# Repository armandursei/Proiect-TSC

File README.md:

# OpenBook e-Reader

Hardware design of **OpenBook**, a low-power, open-source e-book reader built around the
**ESP32-C6** (Wi-Fi 6 + Bluetooth LE, RISC-V). The repository contains the complete design
package: schematic and 2-layer PCB, manufacturing outputs (Gerbers, BOM, pick-and-place) and the
3D mechanical assembly of the device (enclosure, e-paper display, Li-Po battery and PCB).

## Highlights

- **ESP32-C6-WROOM-1-N8** module with the antenna at the board edge and a copper keep-out
  (board cut-out) under it for RF performance.
- **E-paper display** driven over SPI through a 24-pin FPC connector, with the panel's booster
  circuit on board.
- **64 MB external NOR Flash** (W25Q512JV) for books, fonts and images, plus a **microSD** socket.
- **Li-Po power system**: USB-C charging (MCP73831), battery fuel gauge (MAX17048), 3.3 V LDO,
  ESD and overvoltage protection.
- **DS3231 RTC** with supercapacitor backup, able to wake the MCU from deep sleep.
- **BME688 environmental sensor** and a **Qwiic / STEMMA QT** connector for I2C expansion.
- **Single-sided assembly**: all components on the top layer, mostly 0402 SMD, clearly labelled
  test pads for SPI, I2C, UART and power rails.
- Full **3D integration** in Fusion 360 to check fit and clearances between PCB, display,
  battery and enclosure before prototyping.

## Board specifications

| Parameter | Value |
|-----------|-------|
| Layers | 2 (solid ground pour with via stitching) |
| Board outline | 170.2 mm x 111.2 mm |
| Board thickness | 1.67 mm |
| Component placement | Top layer only |
| Trace width | 0.3 mm power, 0.15 mm minimum for signals |
| Supply | 3.3 V from LDO, Li-Po battery charged over USB-C |

## Block diagram

## Key components

The full, EDA-exported bill of materials is in
[`Manufacturing/Bill_of_Materials.csv`](Manufacturing/Bill_of_Materials.csv).

| Ref | Part | Function | Datasheet |
|-----|------|----------|-----------|
| U2 | ESP32-C6-WROOM-1-N8 | Main MCU module (RISC-V, up to 160 MHz, 8 MB flash, Wi-Fi 6, BLE 5) | [PDF](https://www.snapeda.com/parts/ESP32-C6-WROOM-1-N8/Espressif%20Systems/datasheet/) |
| U1 | Winbond W25Q512JVEIQ | 512 Mbit (64 MB) SPI NOR Flash | [PDF](https://www.snapeda.com/parts/W25Q512JVEIQ/Winbond%20Electronics/datasheet/) |
| U3 | Analog Devices DS3231SN# | Temperature-compensated I2C RTC | [PDF](https://www.snapeda.com/parts/DS3231SN%23/Analog%20Devices/datasheet/) |
| C10_SUPERCAP | Seiko CPH3225A | 11 mF supercapacitor (RTC backup) | [PDF](https://mm.digikey.com/Volume0/opasdata/d220001/medias/docus/6537/rev05-CPHCPM.pdf) |
| U4 | Analog Devices MAX17048G+T10 | Li-Po fuel gauge | [PDF](https://www.snapeda.com/parts/MAX17048G+T10/Analog%20Devices/datasheet/) |
| U5 | Microchip MCP73831 | Single-cell Li-Po charge controller | [PDF](https://datasheet.datasheetarchive.com/originals/distributors/Datasheets-DGA15/727147.pdf) |
| IC4 | Torex XC6220A331MR-G | 3.3 V LDO regulator | [PDF](https://product.torexsemi.com/system/files/series/xc6220.pdf) |
| IC1 | ROHM BD5229G-TR | Voltage detector with adjustable delay (reset) | [PDF](https://datasheet.datasheetarchive.com/originals/distributors/Datasheets_SAMA/f2b9741ef86007909f138d561a359946.pdf) |
| SENSOR2 | Bosch BME688 | Temperature, pressure, humidity and VOC sensor | [PDF](https://www.snapeda.com/parts/BME680/Bosch%20Sensortec/datasheet/) |
| J1 | Hirose FH34SRJ-24S-0.5SH(99) | 24-pin 0.5 mm FPC connector for the e-paper panel | [PDF](https://www.hirose.com/en/product/document?clcode=CL0580-1255-6-99&productname=FH34SRJ-24S-0.5SH(99)&series=FH34SRJ&documenttype=2DDrawing&lang=en&documentid=0000990903) |
| L1, D3-D5, Q3 | Wurth 744043680, MBR0530, Si1308EDL | E-paper booster circuit (68 uH inductor, Schottky diodes, N-MOSFET) | [L1](https://download.siliconexpert.com/pdfs/2018/1/3/16/30/56/604/weg_/manual/401950550574837744043680.pdf), [D](https://www.onsemi.com/pdf/datasheet/mbr0530-d.pdf), [Q3](https://componentsearchengine.com/Datasheets/1/SI1308EDL-T1-GE3.pdf) |
| J2 | GCT USB4110-GF-A | USB 2.0 Type-C receptacle | [PDF](https://gct.co/files/drawings/usb4110.pdf) |
| D1 | ST USBLC6-2SC6Y | USB ESD protection | [PDF](https://componentsearchengine.com/Datasheets/1/USBLC6-2SC6Y.pdf) |
| PFMF.050.1 | TDK B72520T0350K062 | Varistor (overvoltage protection) | [PDF](https://datasheet.datasheetarchive.com/originals/distributors/Datasheets_SAMA/81dc50a8c35dfdf39bcf4cbe36cdf37d.pdf) |
| D6, D8-D12 | Littelfuse PGB1010603MR | ESD suppressors | [PDF](https://www.snapeda.com/parts/PGB1010603MR/Littelfuse%20Inc./datasheet/) |
| Q1, Q2 | Diodes DMG2305UX-7 | P-channel MOSFETs | [PDF](https://www.diodes.com/assets/Datasheets/DMG2305UX.pdf) |
| J3 | JST SM04B-SRSS-TB | Qwiic / STEMMA QT I2C connector | [PDF](https://www.snapeda.com/parts/SM04B-SRSS-TB(LF)(SN)/JST%20Sales/datasheet/) |
| J4 | Attend 112A-TAAR-R03 | microSD card socket (push-push) | [PDF](https://www.attend.com.tw/data/download/file/112A-TAAR-R03.pdf) |
| RESET / BOOT / CHANGE | Panasonic EVQPUJ02K | Side-actuated tactile buttons | [PDF](https://www.alldatasheet.com/datasheet-pdf/view/537835/PANASONIC/EVQPUJ02K.html) |
| CHG_LED | Kingbright KP-1608SURCK | Charge status LED | [PDF](https://www.snapeda.com/parts/KP-1608SURCK/Kingbright/datasheet/) |

## How it works

### Interfaces

| Peripheral | Bus | Signals |
|------------|-----|---------|
| E-paper display | SPI | MOSI, MISO, SCK, CS, DC, BUSY, RST |
| External NOR Flash | SPI (shared with the display) | MOSI, MISO, SCK, CS |
| RTC (DS3231) | I2C | SDA, SCL |
| BME688 sensor | I2C | SDA, SCL |
| Qwiic expansion port | I2C | SDA, SCL |
| Charge controller | USB | VBUS, GND, STAT LED |

### ESP32-C6 pin assignment

| Peripheral | ESP32-C6 pin | Function | Rationale |
|------------|--------------|----------|-----------|
| E-paper display | IO4 / IO5 / IO6 | MOSI / MISO / SCK | Fast SPI transfers for screen updates |
| | IO7 | Chip select | Separates the display from the Flash on the shared bus |
| | IO8 | Data/Command (DC) | Switches between data and command mode |
| | IO9 | Reset (RST) | Hardware reset for display initialisation |
| | IO10 | BUSY | Lets the MCU poll the panel state without blocking |
| External Flash | IO4 / IO5 / IO6 | MOSI / MISO / SCK | Shares the SPI bus with the display to save pins |
| | IO11 | Chip select | Dedicated CS for the Flash |
| RTC + BME688 | IO18 / IO19 | SDA / SCL | Shared I2C bus; the two devices have different addresses |
| Reset button | EN | Reset | Native ESP32 hardware reset |
| Boot button | IO0 | Boot | Enters download mode for flashing firmware |
| Charge status | IO13 | GPIO | Visual indication of the charging state |
| Debug UART (test pads) | IO16 / IO17 | TXD0 / RXD0 | Debugging without extra connectors |

### Power management

- The e-paper panel only draws power while the image is refreshed.
- The ESP32-C6 spends idle time in deep sleep; the RTC can wake it at programmed intervals.
- A low-ripple 3.3 V LDO supplies the system, with 100 nF decoupling placed close to every IC
  supply pin.

Estimated current consumption (design estimates, not measurements):

| State | Estimated current |
|-------|-------------------|
| Wi-Fi active + e-paper update | ~180-250 mA |
| Standby with RTC running | ~10-20 uA |
| Deep sleep | ~2.5 uA |

## Design process

The design started from a set of requirements given by the system architect (routing rules,
dimensions, component placement and EMC guidelines). Priorities were a compact PCB without
compromising RF performance, clean and stable power for every module, and extensibility through
the Qwiic connector.

1. **Schematic** (Fusion Electronics): all required blocks (ESP32-C6, RTC, BME688, charger, NOR
   Flash, e-paper), ESD protection on sensitive lines and decoupling on every supply.
2. **PCB layout**: top-side placement only, antenna at the board edge with no copper under it,
   ground pours with dense via stitching around the ESP32, short SPI traces to the display
   connector, test pads labelled on the silkscreen.
3. **Design review**: manual check of critical power and communication traces, plus DRC and ERC.
4. **Manufacturing outputs**: Gerber files, BOM and pick-and-place file.
5. **3D integration**: 3D models of the e-paper display and Li-Po battery were created and the
   PCB was fitted into the existing enclosure, checking display centring, USB-C access, a clear
   antenna area and collisions between PCB, display and housing.

### Problems solved

- **Crowding around the ESP32-C6**: components were rearranged to avoid vias on critical power
  traces while keeping high-speed signals short.
- **Ground pour overlapping the antenna area**: the pour outline was adjusted so the area under
  the antenna is completely free of copper.
- **Clearance in dense areas** (e.g. the e-paper connector): a reduced minimum clearance was
  accepted where modern fabrication tolerances allow it, and verified with DRC.
- **Long SPI traces to the display**: the display connector and its passives were placed as close
  to the ESP32 as the layout allowed.

### Revision history

- Initial: functional placement without mechanical optimisation.
- Rev 1: power routing optimised to avoid vias on power lines.
- Rev 2: ESP32 antenna layout improved, all copper removed under the antenna.
- Rev 3: clearance checks and test pad markings added.
- Final: 3D integration and full assembly check.

### Possible improvements

- Additional internal connectors for hardware extensions (e.g. audio).
- A more robust mechanical retention for the battery.
- Ferrite beads on critical supply lines for further EMC improvement.

## Gallery

| | |
|---|---|
|  |  |
| PCB, top view | PCB, 3D view |
|  |  |
| PCB, 3D view from the opposite corner | PCB, bottom view (ground pour) |
|  |  |
| PCB bottom, 3D view | PCB fitted inside the enclosure |
|  |  |
| Exploded view (top) | Exploded view (3D) |
|  |  |
| E-paper display model | Li-Po battery model |
|  |  |
| Assembled device, front | Assembled device, back |

## Tools

- **Autodesk Fusion Electronics 9.7** (EAGLE-format `.sch` / `.brd`) for schematic and PCB layout
- **Autodesk Fusion 360** for the mechanical design and 3D assembly (`.f3z`, STEP export)

## Opening the design

- **Schematic / PCB**: open `Hardware/OpenBook_Schematic.sch` and `Hardware/OpenBook_PCB_vf.brd`
  in Fusion Electronics or EAGLE 9.x (KiCad can also import EAGLE files).
- **Fabrication**: `Manufacturing/gerbers.zip` contains the Gerber set (copper, solder mask, paste,
  silkscreen, board profile and a Gerber job file) ready to upload to a PCB fab.
- **Assembly**: `Manufacturing/Bill_of_Materials.csv` and `Manufacturing/Pick_and_Place.csv`
  (centroid coordinates in mm).
- **Mechanical**: `Mechanical/EBook_3D_vf.f3z` opens in Fusion 360; `Mechanical/Exploded_EBook_vf.step.zip`
  contains a STEP model of the exploded assembly for any CAD tool.

This repository covers the hardware only; no firmware is included.

## Project structure

```
.
├── Hardware/
│   ├── OpenBook_Schematic.sch      # Schematic (Fusion Electronics / EAGLE)
│   └── OpenBook_PCB_vf.brd         # Final PCB layout
├── Manufacturing/
│   ├── Bill_of_Materials.csv       # BOM exported from the EDA tool
│   ├── Pick_and_Place.csv          # Component placement (centroid) file
│   └── gerbers.zip                 # Gerber files for fabrication
├── Mechanical/
│   ├── EBook_3D_vf.f3z             # Fusion 360 assembly (enclosure, PCB, display, battery)
│   └── Exploded_EBook_vf.step.zip  # STEP model of the exploded assembly
├── Images/                         # Renders of the PCB and the assembled device
└── LICENSE
```

## License

Licensed under the [Apache License 2.0](LICENSE).

## Author

George-Armand Ursei - [GitHub](https://github.com/armandursei)

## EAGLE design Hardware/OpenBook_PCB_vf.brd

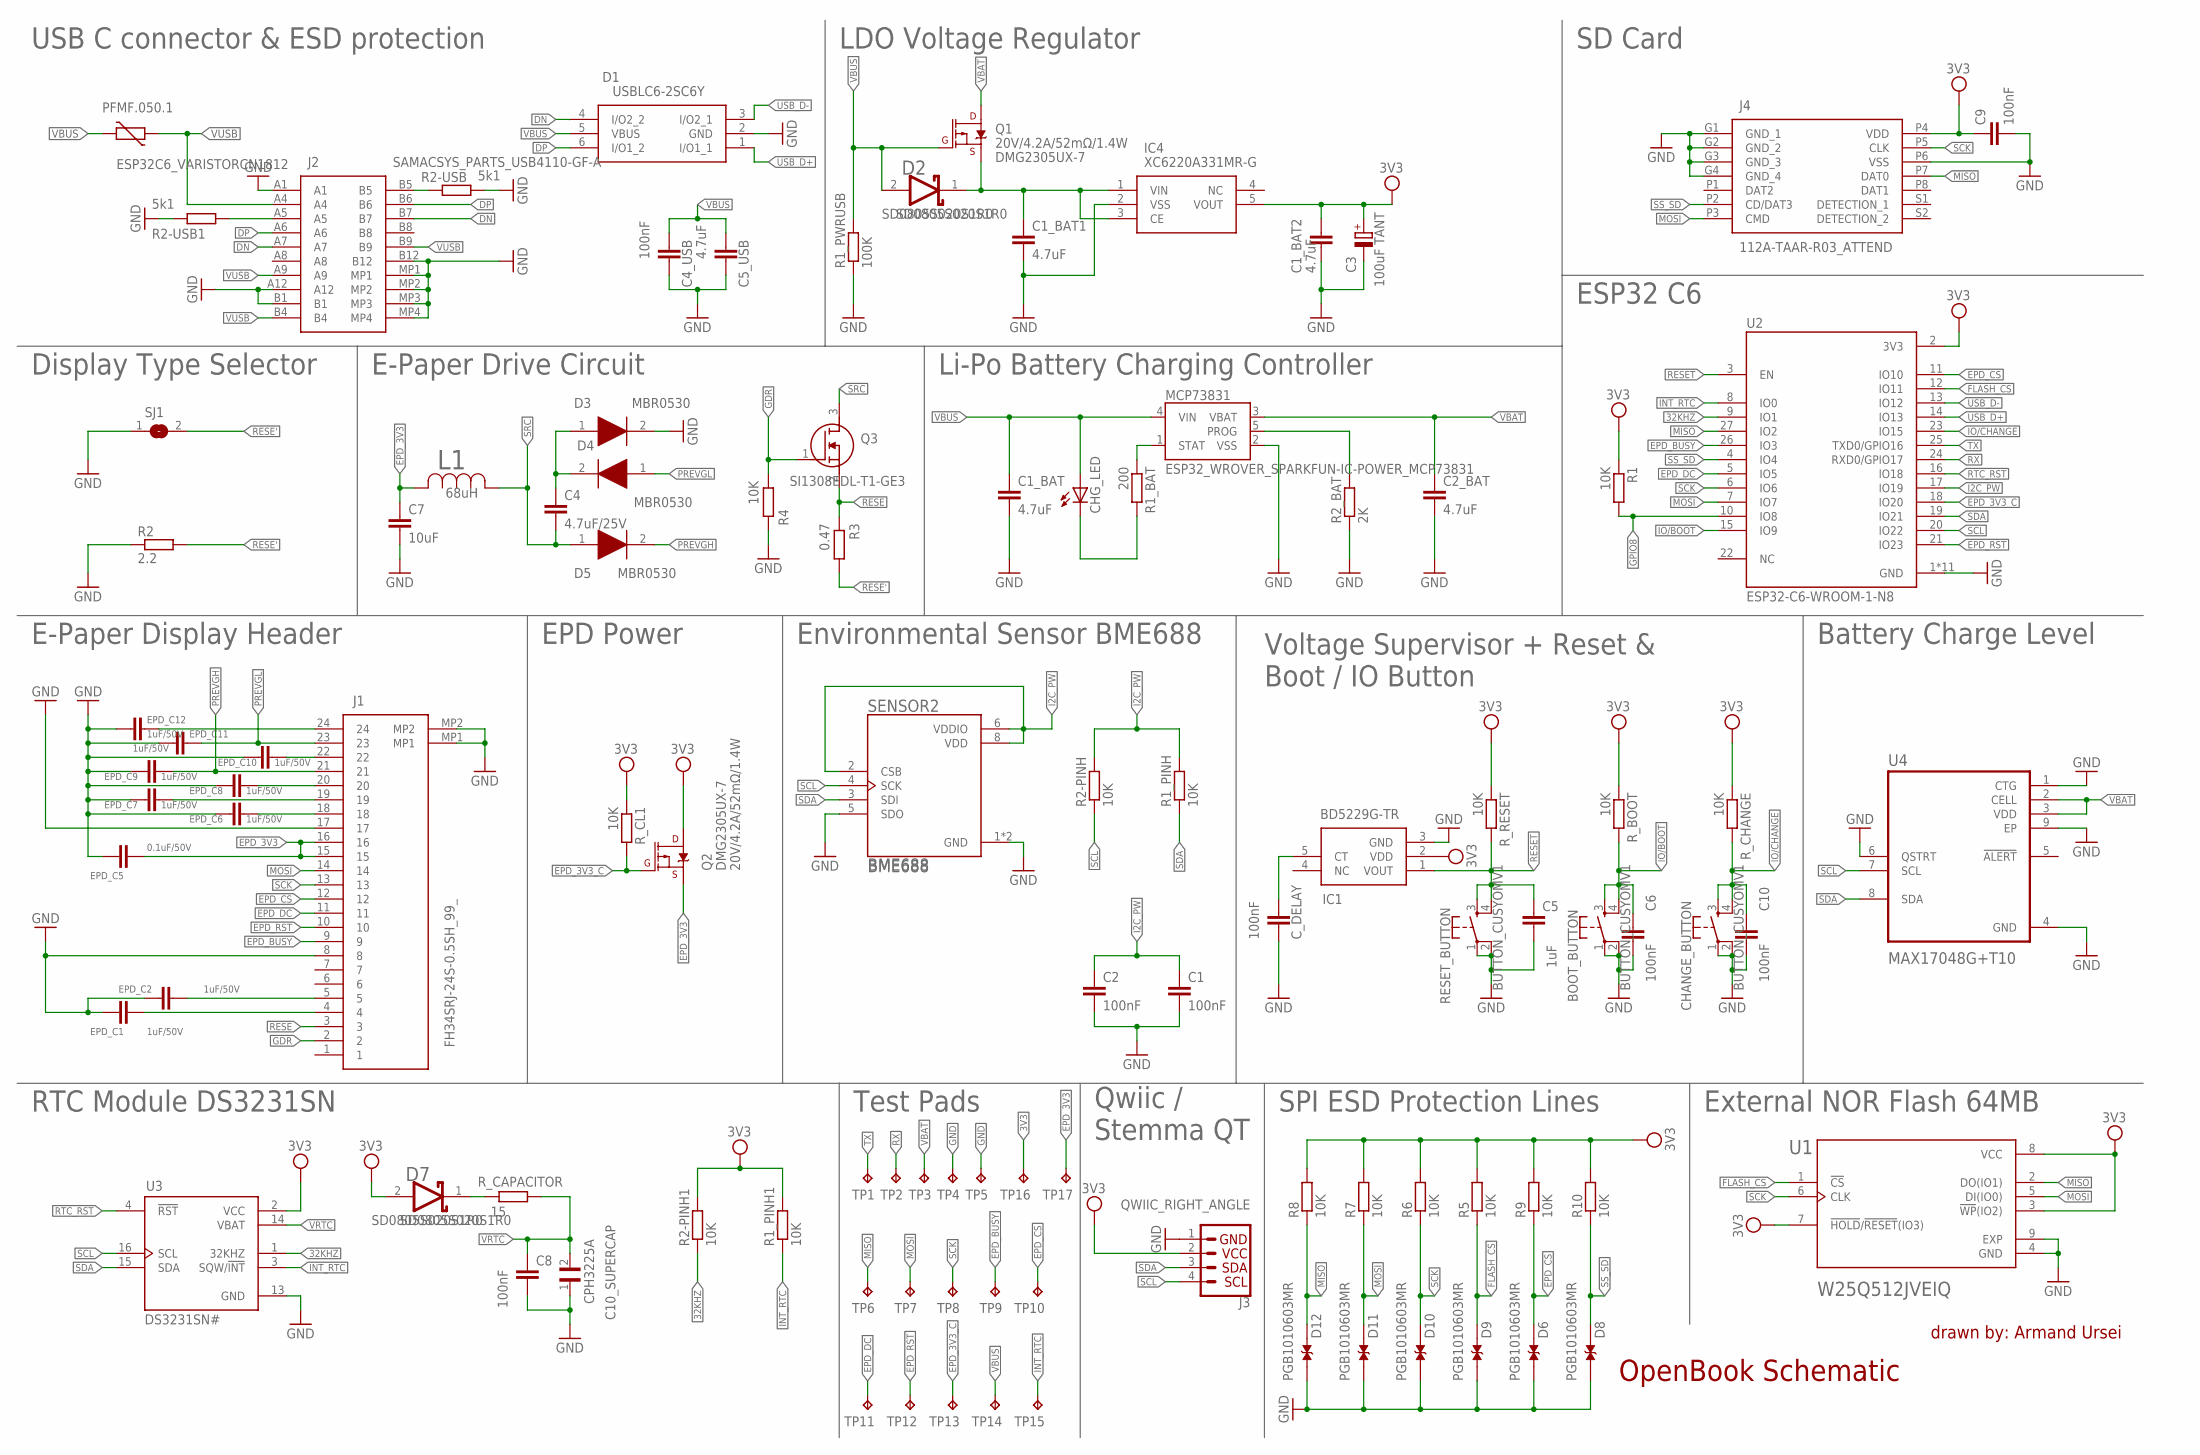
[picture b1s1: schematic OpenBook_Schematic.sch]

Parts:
BOOT_BUTTON: BUTTON_CUSYOMV1; MYBUTTON
C1, C2, C4_USB, C6, C8, C9, C10: 100nF; ESP32_WROVER_EAGLE-LTSPICE_C0402
C1_BAT, C1_BAT1, C1_BAT2, C2_BAT, C5_USB: 4.7uF; ESP32_WROVER_EAGLE-LTSPICE_C0402
C3: 100uF TANT; RCL_CT3528
C4: 4.7uF/25V; ESP32_WROVER_EAGLE-LTSPICE_C0402
C5: 1uF; ESP32_WROVER_EAGLE-LTSPICE_C0402
C7: 10uF; ESP32_WROVER_EAGLE-LTSPICE_C0402
C10_SUPERCAP: CPH3225A; CAPCP3225X100N
CHANGE_BUTTON: BUTTON_CUSYOMV1; MYBUTTON
CHG_LED: ADAFRUIT_LEDCHIP-LED0603; ADAFRUIT_CHIP-LED0603
C_DELAY: 100nF; ESP32_WROVER_EAGLE-LTSPICE_C0402
D1: USBLC6-2SC6Y; SOT95P280X145-6N
D2, D7: SD0805S020S1R0; ESP32_WROVER_AVX---SD0805S020S1R0_AVX_SD0805S020S1R0_0
D3, D4, D5: MBR0530; SOD3716X135N
D6, D8, D9, D10, D11, D12: PGB1010603MR; DIOC1608X36N
EPD_C1, EPD_C2, EPD_C6, EPD_C7, EPD_C8, EPD_C9, EPD_C10, EPD_C11, EPD_C12: 1uF/50V; ESP32_WROVER_EAGLE-LTSPICE_C0402
EPD_C5: 0.1uF/50V; ESP32_WROVER_EAGLE-LTSPICE_C0402
IC1: BD5229G-TR; SOT95P280X125-5N
IC4: XC6220A331MR-G; SOT95P280X120-5N
J1: FH34SRJ-24S-0.5SH_99_; FH34SRJ24S05SH99
J2: SAMACSYS_PARTS_USB4110-GF-A; SAMACSYS_PARTS_USB4110GFA
J3: QWIIC_RIGHT_ANGLE; JST04_1MM_RA
J4: 112A-TAAR-R03_ATTEND; 112ATAARR03ATTEND
L1: 68uH; IND_4828-WE-TPC_WRE
MCP73831: ESP32_WROVER_SPARKFUN-IC-POWER_MCP73831; ESP32_WROVER_SPARKFUN-IC-POWER_SOT23-5
PFMF.050.1: ESP32C6_VARISTORCN1812; ESP32C6_VARISTOR_CT/CN1812
Q1, Q2: 20V/4.2A/52mΩ/1.4W; ESP32_WROVER_SPARKFUN-DISCRETESEMI_SOT23-3
Q3: SI1308EDL-T1-GE3; SOT65P210X110-3N
R1, R1_PINH, R1_PINH1, R2-PINH, R2-PINH1, R4, R5, R6, R7, R8, R9, R10: 10K; ESP32_WROVER_EAGLE-LTSPICE_R0402
R1_BAT: 200; ESP32_WROVER_EAGLE-LTSPICE_R0402
R1_PWRUSB: 100K; ESP32_WROVER_EAGLE-LTSPICE_R0402
R2: 2.2; ESP32_WROVER_EAGLE-LTSPICE_R0402
R2-USB, R2-USB1: 5k1; ESP32_WROVER_EAGLE-LTSPICE_R0402
R2_BAT: 2K; ESP32_WROVER_EAGLE-LTSPICE_R0402
R3: 0.47; ESP32_WROVER_EAGLE-LTSPICE_R0402
RESET_BUTTON: BUTTON_CUSYOMV1; MYBUTTON
R_BOOT: 10K; ESP32_WROVER_EAGLE-LTSPICE_R0402
R_CAPACITOR: 15; ESP32_WROVER_EAGLE-LTSPICE_R0402
R_CHANGE: 10K; ESP32_WROVER_EAGLE-LTSPICE_R0402
R_CL1: 10K; ESP32_WROVER_EAGLE-LTSPICE_R0402
R_RESET: 10K; ESP32_WROVER_EAGLE-LTSPICE_R0402
SENSOR2: BME688; ESP32_WROVER_BME680_PSON80P300X300X100-8N
SJ1: SJ
TP1, TP2, TP3, TP4, TP5, TP6, TP7, TP8, TP9, TP10, TP11, TP12, TP13, TP14, TP15, TP16, TP17: TPTP20R; TP20R
U1: W25Q512JVEIQ; SON127P600X800X80-9N
U2: ESP32-C6-WROOM-1-N8; XCVR_ESP32-C6-WROOM-1-N8
U3: DS3231SN#; SOIC127P1032X265-16N
U4: MAX17048G+T10; SON50P200X200X80-9N

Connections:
3V3: C1_BAT2.1, C3.+, C9.1, D7.2 (ANODE), IC1.2 (VDD), IC4.5 (VOUT), J3.2, J4.P4 (VDD), Q2.3 (D), R1.1, R1_PINH1.2, R2-PINH1.2, R5.2, R6.2, R7.2, R8.2, R9.2, R10.2, R_BOOT.1, R_CHANGE.1, R_CL1.1, R_RESET.1, TP16.TP, U1.3 (!WP!(IO2)), U1.7 (!HOLD!/!RESET!(IO3)), U1.8 (VCC), U2.2 (3V3), U3.2 (VCC)
32KHZ: R2-PINH1.1, U2.9 (IO1), U3.1 (32KHZ)
DN: D1.4 (I/O2_2), J2.A7, J2.B7
DP: D1.6 (I/O1_2), J2.A6, J2.B6
EPD_3V3: C7.1, EPD_C5.1, J1.15, J1.16, L1.2, Q2.2 (S), TP17.TP
EPD_3V3_C: Q2.1 (G), R_CL1.2, TP13.TP, U2.18 (IO20)
EPD_BUSY: J1.9, TP9.TP, U2.26 (IO3)
EPD_CS: D6.2, J1.12, R9.1, TP10.TP, U2.11 (IO10)
EPD_DC: J1.11, TP11.TP, U2.5 (IO5)
EPD_RST: J1.10, TP12.TP, U2.21 (IO23)
FLASH_CS: D9.2, R5.1, U1.1 (!CS), U2.12 (IO11)
GDR: J1.2, Q3.1 (G), R4.1
GND: BOOT_BUTTON.1, BOOT_BUTTON.2, C1.2, C1_BAT.2, C1_BAT1.2, C1_BAT2.2, C2.2, C2_BAT.2, C3.-, C4_USB.2, C5.2, C5_USB.2, C6.2, C7.2, C8.2, C9.2, C10.2, C10_SUPERCAP.1, CHANGE_BUTTON.1, CHANGE_BUTTON.2, C_DELAY.2, D1.2 (GND), D3.2 (K), D6.1, D8.1, D9.1, D10.1, D11.1, D12.1, EPD_C1.2, EPD_C2.2, EPD_C5.2, EPD_C6.2, EPD_C7.2, EPD_C8.2, EPD_C9.2, EPD_C10.2, EPD_C11.2, EPD_C12.2, IC1.3 (GND), IC4.2 (VSS), J1.8, J1.17, J1.MP1, J1.MP2, J2.A1, J2.A12, J2.B1, J2.B12, J2.MP1, J2.MP2, J2.MP3, J2.MP4, J3.1, J4.G1 (GND_1), J4.G2 (GND_2), J4.G3 (GND_3), J4.G4 (GND_4), J4.P6 (VSS), MCP73831.2 (VSS), R1_PWRUSB.1, R2.1, R2-USB.2, R2-USB1.1, R2_BAT.1, R4.2, RESET_BUTTON.1, RESET_BUTTON.2, SENSOR2.1 (GND), SENSOR2.5 (SDO), SENSOR2.7 (GND), SJ1.1, TP4.TP, TP5.TP, U1.4 (GND), U1.9 (EXP), U2.1 (GND), U2.28 (GND), U2.29_1 (GND), U2.29_2 (GND), U2.29_3 (GND), U2.29_4 (GND), U2.29_5 (GND), U2.29_6 (GND), U2.29_7 (GND), U2.29_8 (GND), U2.29_9 (GND), U3.13 (GND), U4.1 (CTG), U4.4 (GND), U4.6 (QSTRT), U4.9 (EP)
GPIO8: R1.2, U2.10 (IO8)
I2C_PW: C1.1, C2.1, R1_PINH.2, R2-PINH.2, SENSOR2.2 (CSB), SENSOR2.6 (VDDIO), SENSOR2.8 (VDD), U2.17 (IO19)
INT_RTC: R1_PINH1.1, TP15.TP, U2.8 (IO0), U3.3 (SQW/!INT)
IO/BOOT: BOOT_BUTTON.3, BOOT_BUTTON.4, C6.1, R_BOOT.2, U2.15 (IO9)
IO/CHANGE: C10.1, CHANGE_BUTTON.3, CHANGE_BUTTON.4, R_CHANGE.2, U2.23 (IO15)
MISO: D12.2, J4.P7 (DAT0), R8.1, TP6.TP, U1.2 (DO(IO1)), U2.27 (IO2)
MOSI: D11.2, J1.14, J4.P3 (CMD), R7.1, TP7.TP, U1.5 (DI(IO0)), U2.7 (IO7)
unnamed: J2.A5, R2-USB1.2
unnamed: C1_BAT1.1, D2.1 (CATHODE), IC4.1 (VIN), IC4.3 (CE), Q1.2 (S)
unnamed: MCP73831.1 (STAT), R1_BAT.1
unnamed: CHG_LED.C, R1_BAT.2
unnamed: C4.1, D3.1 (A), D4.2 (K)
unnamed: EPD_C12.1, J1.24
unnamed: J2.B5, R2-USB.1
unnamed: MCP73831.5 (PROG), R2_BAT.2
unnamed: EPD_C10.1, J1.22
unnamed: EPD_C8.1, J1.20
unnamed: EPD_C7.1, J1.19
unnamed: EPD_C6.1, J1.18
unnamed: C_DELAY.1, IC1.5 (CT)
unnamed: D7.1 (CATHODE), R_CAPACITOR.2
unnamed: EPD_C2.1, J1.5
unnamed: EPD_C1.1, J1.4
PREVGH: D5.2 (K), EPD_C9.1, J1.21
PREVGL: D4.1 (A), EPD_C11.1, J1.23
RESE: J1.3, Q3.2 (S), R3.1
RESE': R2.2, R3.2, SJ1.2
RESET: C5.1, IC1.1 (VOUT), RESET_BUTTON.3, RESET_BUTTON.4, R_RESET.2, U2.3 (EN)
RTC_RST: U2.16 (IO18), U3.4 (!RST)
RX: TP2.TP, U2.24 (RXD0/GPIO17)
SCK: D10.2, J1.13, J4.P5 (CLK), R6.1, TP8.TP, U1.6 (CLK), U2.6 (IO6)
SCL: J3.4, R2-PINH.1, SENSOR2.4 (SCK), U2.20 (IO22), U3.16 (SCL), U4.7 (SCL)
SDA: J3.3, R1_PINH.1, SENSOR2.3 (SDI), U2.19 (IO21), U3.15 (SDA), U4.8 (SDA)
SRC: C4.2, D5.1 (A), L1.1, Q3.3 (D)
SS_SD: D8.2, J4.P2 (CD/DAT3), R10.1, U2.4 (IO4)
TX: TP1.TP, U2.25 (TXD0/GPIO16)
USB_D+: D1.1 (I/O1_1), U2.14 (IO13)
USB_D-: D1.3 (I/O2_1), U2.13 (IO12)
VBAT: C2_BAT.1, MCP73831.3 (VBAT), Q1.3 (D), TP3.TP, U4.2 (CELL), U4.3 (VDD)
VBUS: C1_BAT.1, C4_USB.1, C5_USB.1, CHG_LED.A, D1.5 (VBUS), D2.2 (ANODE), MCP73831.4 (VIN), PFMF.050.1.2, Q1.1 (G), R1_PWRUSB.2, TP14.TP
VRTC: C8.1, C10_SUPERCAP.2, R_CAPACITOR.1, U3.14 (VBAT)
VUSB: J2.A4, J2.A9, J2.B4, J2.B9, PFMF.050.1.1

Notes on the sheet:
USB C connector & ESD protection
DMG2305UX-7
SD0805S020S1R0
Display Type Selector
LDO Voltage Regulator
SD Card
E-Paper Drive Circuit
Li-Po Battery Charging Controller
ESP32 C6
E-Paper Display Header
EPD Power
BME688
Environmental Sensor BME688
Voltage Supervisor + Reset & Boot / IO Button
Battery Charge Level
RTC Module DS3231SN
Test Pads
Qwiic / Stemma QT
SPI ESD Protection Lines
External NOR Flash 64MB
drawn by: Armand Ursei
OpenBook Schematic

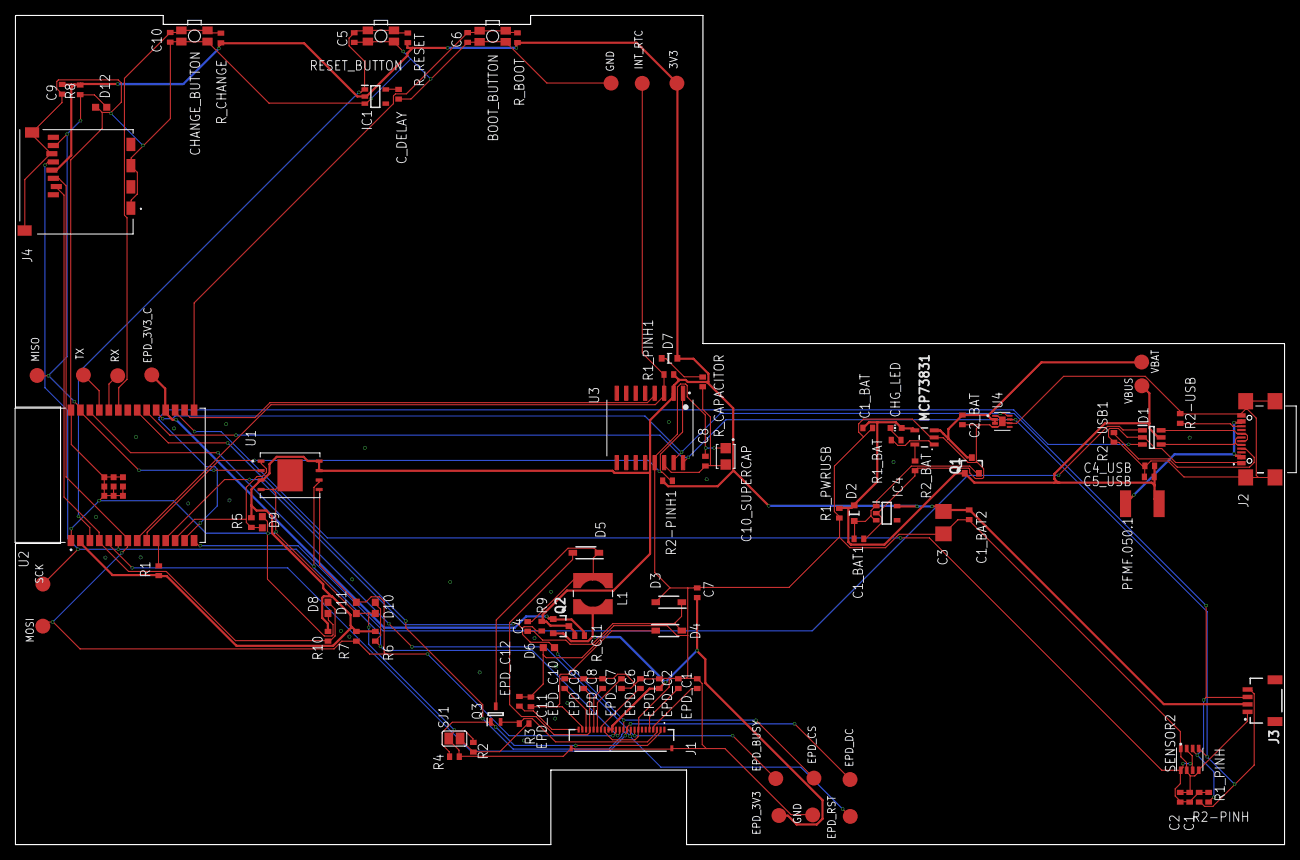
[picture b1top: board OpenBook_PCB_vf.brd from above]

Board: 2 copper layers, 170.2 x 111.2 mm, 103 parts (0 on the bottom side), 55 nets.

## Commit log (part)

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2025-04-06 Create LICENSE
2025-04-06 +Manufacturing, Images, Mechanical, Hardware files
2025-04-06 Rename Bill_of_Materials.bom.csv to Bill_of_Materials.csv
2025-04-15 Updated 3D
2025-04-15 Updated Exploded 3D

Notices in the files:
parts and their libraries:
COPYRIGHT: Copyright (C) 2024 Ultra Librarian. All rights reserved.
